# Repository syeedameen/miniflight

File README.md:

# miniflight
Budget Flight Controller for Drones with ATmega328P Microcontroller

- MPU6050 - Inertial Measurement Unit
- BMP280 - Prassure & temprature sensor
- ATmega328p Microcontroller
- 2-layer PCB design in KiCad EDA (manufactured from JLCPCB)
- 45 x 45 mm PCB size

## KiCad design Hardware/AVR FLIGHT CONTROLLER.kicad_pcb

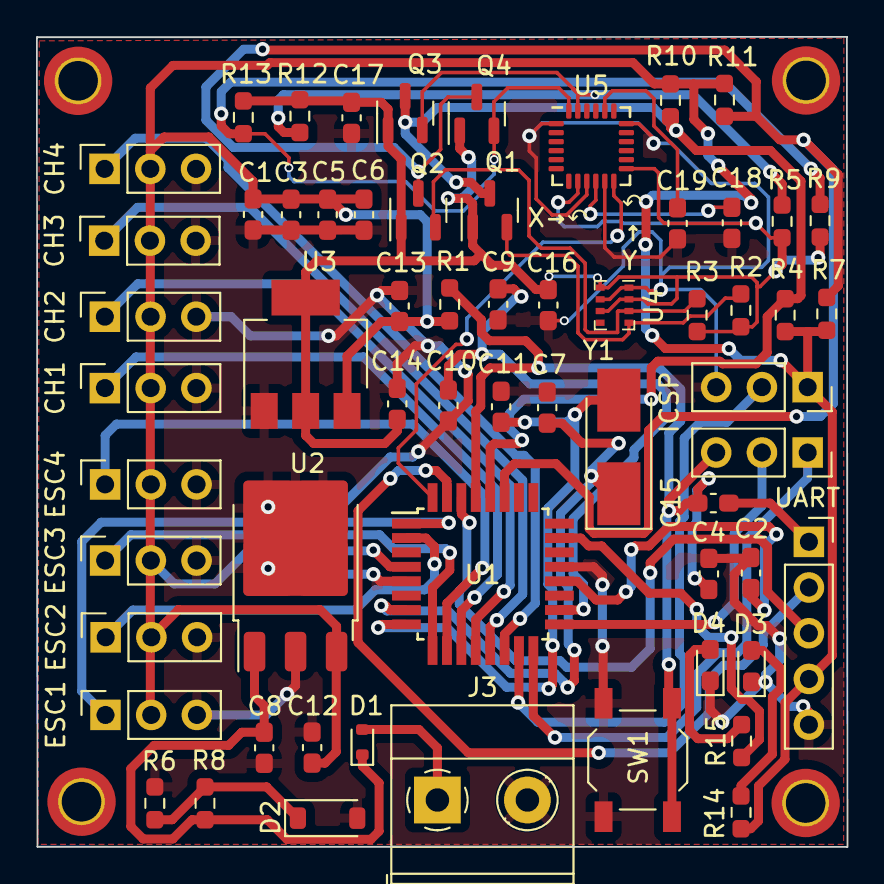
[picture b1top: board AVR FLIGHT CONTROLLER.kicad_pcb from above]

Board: 2 copper layers, 45.0 x 45.0 mm, 65 parts (0 on the bottom side), 37 nets.

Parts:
C1: 4.7uf; C_0603_1608Metric_Pad1.08x0.95mm_HandSolder
C2, C3, C4, C5, C6, C10, C12, C15, C17: 100nf; C_0603_1608Metric_Pad1.08x0.95mm_HandSolder
C7, C11: 22pf; C_0603_1608Metric_Pad1.08x0.95mm_HandSolder
C8: 330nf; C_0603_1608Metric_Pad1.08x0.95mm_HandSolder
C9: 1uf; C_0603_1608Metric_Pad1.08x0.95mm_HandSolder
C13, C14: 10uf; C_0603_1608Metric_Pad1.08x0.95mm_HandSolder
C16: 10nf; C_0603_1608Metric_Pad1.08x0.95mm_HandSolder
C18: 0.1uf; C_0603_1608Metric_Pad1.08x0.95mm_HandSolder
C19: 2.2nf; C_0603_1608Metric_Pad1.08x0.95mm_HandSolder
CH1: CH_1; PinSocket_1x03_P2.54mm_Vertical
CH2: CH_2; PinSocket_1x03_P2.54mm_Vertical
CH3: CH_3; PinSocket_1x03_P2.54mm_Vertical
CH4: CH_4; PinSocket_1x03_P2.54mm_Vertical
D1: 1N4148WT; D_SOD-523
D2: D_Zener; D_SOD-123
D3, D4: LED; LED_0603_1608Metric_Pad1.05x0.95mm_HandSolder
ESC1: ESC_1; PinSocket_1x03_P2.54mm_Vertical
ESC2: ESC_2; PinSocket_1x03_P2.54mm_Vertical
ESC3: ESC_3; PinSocket_1x03_P2.54mm_Vertical
ESC4: ESC_4; PinSocket_1x03_P2.54mm_Vertical
H1, H2, H3, H4: MountingHole; MountingHole_2.2mm_M2_DIN965_Pad_TopBottom
J1: PinSocket_1x03_P2.54mm_Vertical
J2: ICSP; PinSocket_1x03_P2.54mm_Vertical
J3: Power Connector; TerminalBlock_Phoenix_MKDS-1,5-2_1x02_P5.00mm_Horizontal
Q1, Q2, Q3, Q4: BSS138; SOT-23
R1, R2, R3, R4, R5, R7, R8, R9, R10, R11, R12, R13: 10k; R_0603_1608Metric_Pad0.98x0.95mm_HandSolder
R6: 1k; R_0603_1608Metric_Pad0.98x0.95mm_HandSolder
R14, R15: 330; R_0603_1608Metric_Pad0.98x0.95mm_HandSolder
SW1: SW_Push; SW_SPST_TL3342
U1: ATmega328PB-A; TQFP-32_7x7mm_P0.8mm
U2: L7805; TO-252-3_TabPin2
U3: AMS1117-3.3; SOT-223-3_TabPin2
U4: BMP280; Bosch_LGA-8_2x2.5mm_P0.65mm_ClockwisePinNumbering
U5: MPU-6050; InvenSense_QFN-24_4x4mm_P0.5mm
UART: UART; PinSocket_1x05_P2.54mm_Vertical
Y1: Crystal; Crystal_SMD_5032-2Pin_5.0x3.2mm_HandSoldering

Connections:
/+3.3v: C14.1, C16.1, C17.1, Q1.1 (G), Q2.1 (G), Q3.1 (G), Q4.1 (G), R2.1, R3.1, R5.1, R9.1, R12.1, R13.1, U3.2 (VO), U4.2 (CSB), U4.6 (VDDIO), U4.8 (VDD), U5.8 (VLOGIC), U5.13 (VDD)
/+5v: C1.2, C3.2, C5.2, C6.2, C12.1, C13.1, CH1.2, CH2.2, CH3.2, CH4.2, ESC1.2, ESC2.2, ESC3.2, ESC4.2, J1.1, R1.2, R4.1, R7.1, R10.1, R11.1, R14.1, U1.4 (VCC), U2.3 (OUT), U3.3 (VI), UART.4
/BAT+: C8.1, D1.1 (K), R8.1, U2.1 (IN)
/CH1: CH1.1, U1.11 (PD7)
/CH2: CH2.1, U1.12 (PB0)
/CH3: CH3.1, U1.13 (PB1)
/CH4: CH4.1, U1.14 (PB2)
/ESC1: ESC1.1, U1.1 (PD3)
/ESC2: ESC2.1, U1.2 (PD4)
/ESC3: ESC3.1, U1.9 (PD5)
/ESC4: ESC4.1, U1.10 (PD6)
/LED: R15.1, U1.23 (PC0)
/MISO: J2.1, U1.16 (PB4)
/MOSI: J1.2, U1.15 (PB3)
/OSC1: C7.2, U1.7 (XTAL1/PB6), Y1.1
/OSC2: C11.2, U1.8 (XTAL2/PB7), Y1.2
/RESET: C4.2, C15.2, J2.3, R1.1, SW1.2, U1.29 (~RESET/PC6)
/RXD: U1.30 (PD0), UART.3
/SCK: J2.2, U1.17 (PB5)
/SCK_3V_BMP: Q1.2 (S), R2.2, U4.4 (SCK)
/SCL: Q1.3 (D), Q3.3 (D), R4.2, R10.2, U1.28 (PC5)
/SCL_3V_IMU: Q3.2 (S), R5.2, R12.2, U5.23 (SCL)
/SDA: Q2.3 (D), Q4.3 (D), R7.2, R11.2, U1.27 (PC4)
/SDA_3V_IMU: Q4.2 (S), R9.2, R13.2, U5.24 (SDA)
/SDI_3V_BMP: Q2.2 (S), R3.2, U4.3 (SDI)
/TXD: U1.31 (PD1), UART.2
GND: C1.1, C2.1, C3.1, C4.1, C5.1, C6.1, C7.1, C8.2, C9.1, C10.1, C11.1, C12.2, C13.2, C14.2, C16.2, C17.2, C18.2, C19.2, CH1.3, CH2.3, CH3.3, CH4.3, D2.2 (A), D3.1 (K), D4.1 (K), ESC1.3, ESC2.3, ESC3.3, ESC4.3, J1.3, J3.2, R6.2, SW1.1, U1.5 (GND), U1.21 (GND), U2.2 (GND), U3.1 (GND), U4.1 (GND), U4.7 (GND), U5.1 (CLKIN), U5.9 (AD0), U5.11 (FSYNC), U5.18 (GND), UART.5
IMU_INT: U1.32 (PD2), U5.12 (INT)
unnamed: D1.2 (A), J3.1
unnamed: D2.1 (K), R6.1, R8.2
unnamed: D3.2 (A), R14.2
unnamed: D4.2 (A), R15.2
unnamed: C15.1, UART.1
unnamed: C2.2, U1.20 (AREF)
unnamed: C9.2, C10.2, U1.18 (AVCC)
unnamed: C19.1, U5.20 (CPOUT)
unnamed: C18.1, U5.10 (REGOUT)

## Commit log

2024-04-23 update Schematic
